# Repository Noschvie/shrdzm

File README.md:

## SHRDZM is intended to become an end-to-end integration platform.
It provides wiring digrams, source code and working examples.
Also plug-ins for most commonly used home automation solutions will be collected.

To build cheap integrations of many kind of sensors and/or actors into your own automation solution with the focus on energy efficiancy (battery operated devices) and simpleness.

Take a look on the [Wiki](https://github.com/saghonfly/shrdzm/wiki)

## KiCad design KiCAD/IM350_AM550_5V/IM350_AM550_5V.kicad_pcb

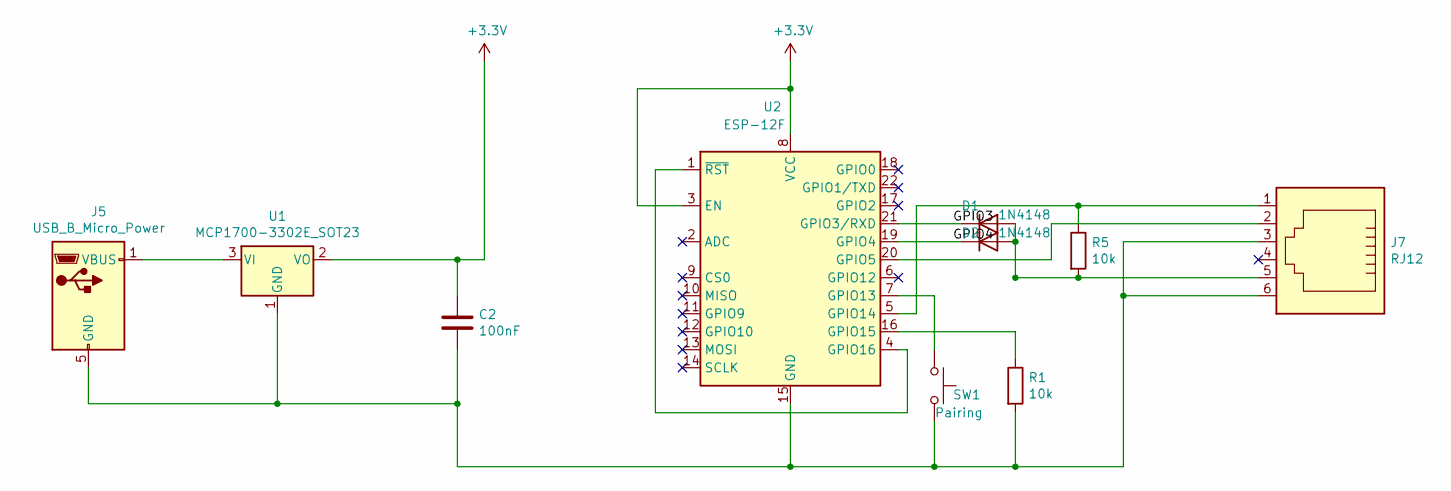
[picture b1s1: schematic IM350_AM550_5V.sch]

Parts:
C2: 100nF; C_Disc_D6.0mm_W2.5mm_P5.00mm
D1, D2: 1N4148; D_0805_2012Metric_Pad1.15x1.40mm_HandSolder
J5: USB_B_Micro_Power; USB_Micro-B_Power
J7: RJ12; RJ12_Amphenol_54601_Reduced
R1, R5: 10k; R_Axial_DIN0207_L6.3mm_D2.5mm_P2.54mm_Vertical
SW1: Pairing; SW_PUSH_6mm
U1: MCP1700-3302E_SOT23; SOT-23_Handsoldering
U2: ESP-12F; ESP-12E

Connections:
+3V3: C2.1, U1.2 (VO), U2.3 (EN), U2.8 (VCC)
/GPIO3: D1.1 (K), U2.21 (GPIO3/RXD)
/GPIO4: D2.1 (K), U2.19 (GPIO4)
unnamed: C2.2, J5.5 (GND), J7.3, J7.6, R1.2, SW1.2, U1.1 (GND), U2.15 (GND)
unnamed: D1.2 (A), D2.2 (A), J7.5, R5.2
unnamed: J5.1 (VBUS), U1.3 (VI)
unnamed: J7.1, R5.1, U2.5 (GPIO14)
unnamed: J7.2, U2.20 (GPIO5)
unnamed: R1.1, U2.16 (GPIO15)
unnamed: SW1.1, U2.7 (GPIO13)
unnamed: U2.1 (~RST), U2.4 (GPIO16)

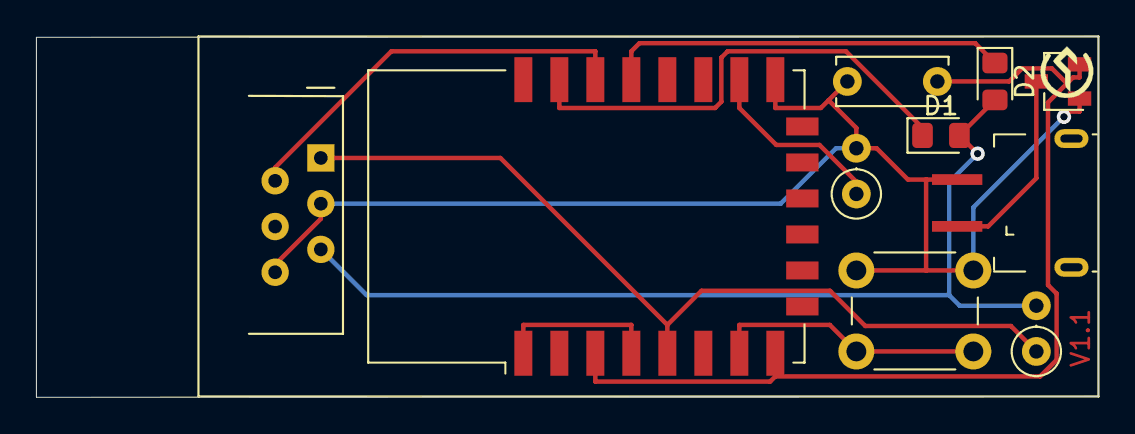
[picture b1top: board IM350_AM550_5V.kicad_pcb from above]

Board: 2 copper layers, 59.0 x 20.0 mm, 12 parts (1 on the bottom side), 11 nets.

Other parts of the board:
G1: LOGO; SHRDZM 22x7
G2: LOGO; SHRDZM Symbol 3x3

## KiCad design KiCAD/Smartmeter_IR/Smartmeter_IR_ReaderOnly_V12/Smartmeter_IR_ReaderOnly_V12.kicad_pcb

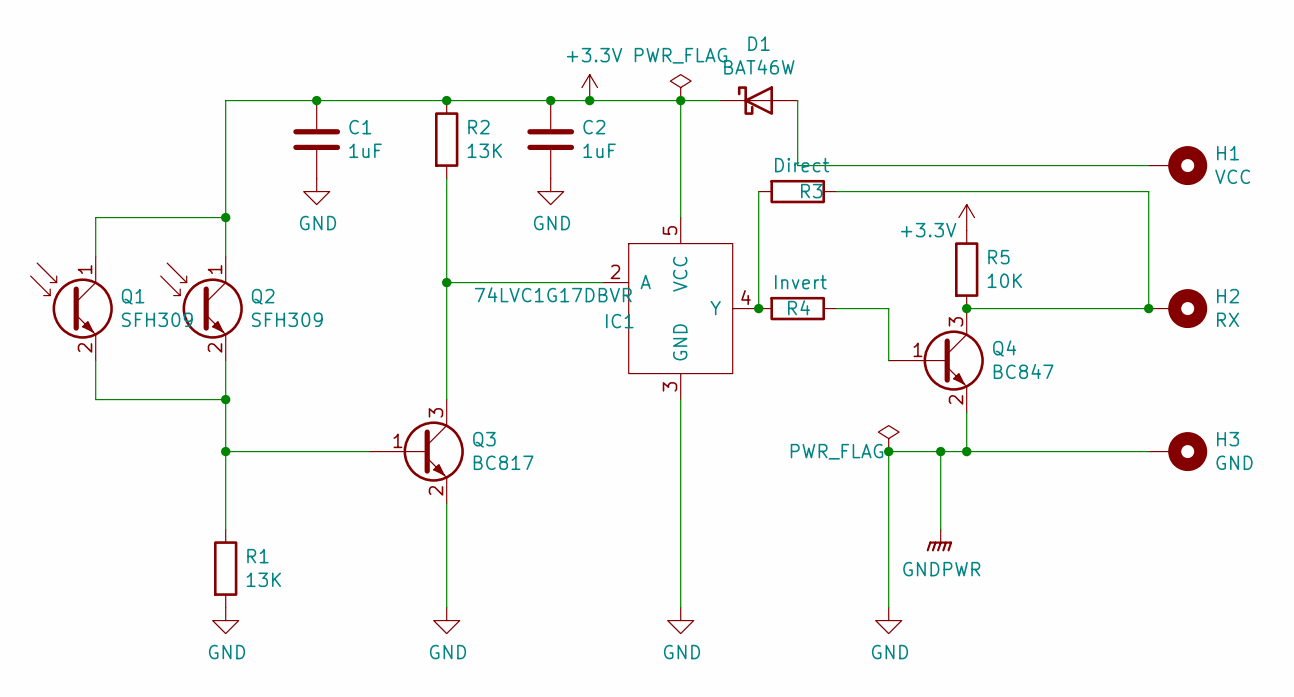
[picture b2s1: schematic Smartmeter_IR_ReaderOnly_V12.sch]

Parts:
C1, C2: 1uF; C_0603_1608Metric_Pad1.08x0.95mm_HandSolder
D1: BAT46W; D_SOD-123
H1: VCC; SolderWirePad_1x01_SMD_1x2mm
H2: RX; SolderWirePad_1x01_SMD_1x2mm
H3: GND; SolderWirePad_1x01_SMD_1x2mm
IC1: 74LVC1G17DBVR; SOT-23-5
Q1, Q2: SFH309; LED_D3.0mm
Q3: BC817; SOT-23
Q4: BC847; SOT-23
R1, R2: 13K; R_0603_1608Metric_Pad0.98x0.95mm_HandSolder
R3: Direct; R_0402_1005Metric_Pad0.72x0.64mm_HandSolder
R4: Invert; R_0402_1005Metric_Pad0.72x0.64mm_HandSolder
R5: 10K; R_0603_1608Metric_Pad0.98x0.95mm_HandSolder

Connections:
+3V3: C1.1, C2.1, D1.1 (K), IC1.5 (VCC), Q1.1 (C), Q2.1 (C), R2.1, R5.1
GND: C1.2, C2.2, H3.1, IC1.3 (GND), Q3.2 (E), Q4.2 (E), R1.2
unnamed: D1.2 (A), H1.1
unnamed: H2.1, Q4.3 (C), R3.1, R5.2
unnamed: IC1.2 (A), Q3.3 (C), R2.2
unnamed: IC1.4 (Y), R3.2, R4.2
unnamed: Q1.2 (E), Q2.2 (E), Q3.1 (B), R1.1
unnamed: Q4.1 (B), R4.1

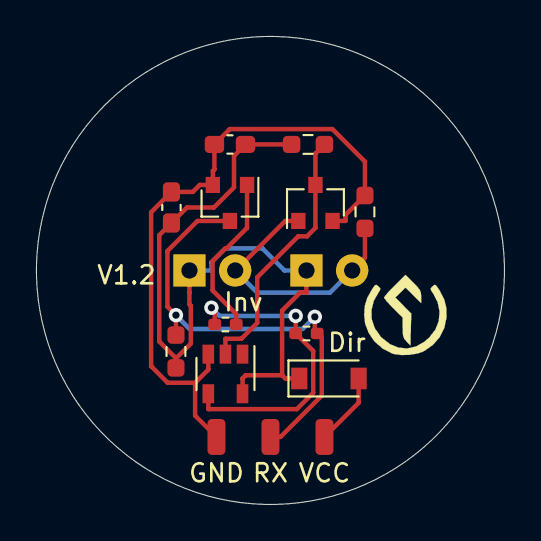
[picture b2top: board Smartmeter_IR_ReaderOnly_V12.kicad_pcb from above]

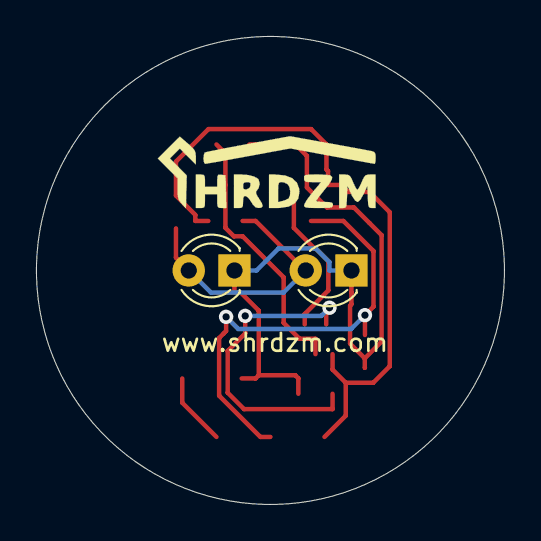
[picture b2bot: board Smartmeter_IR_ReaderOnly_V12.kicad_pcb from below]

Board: 2 copper layers, 26.0 x 26.0 mm, 18 parts (3 on the bottom side), 8 nets.

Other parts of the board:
G1: LOGO; SHRDZM 12x4
G2: LOGO; SHRDZM Symbol 5x5

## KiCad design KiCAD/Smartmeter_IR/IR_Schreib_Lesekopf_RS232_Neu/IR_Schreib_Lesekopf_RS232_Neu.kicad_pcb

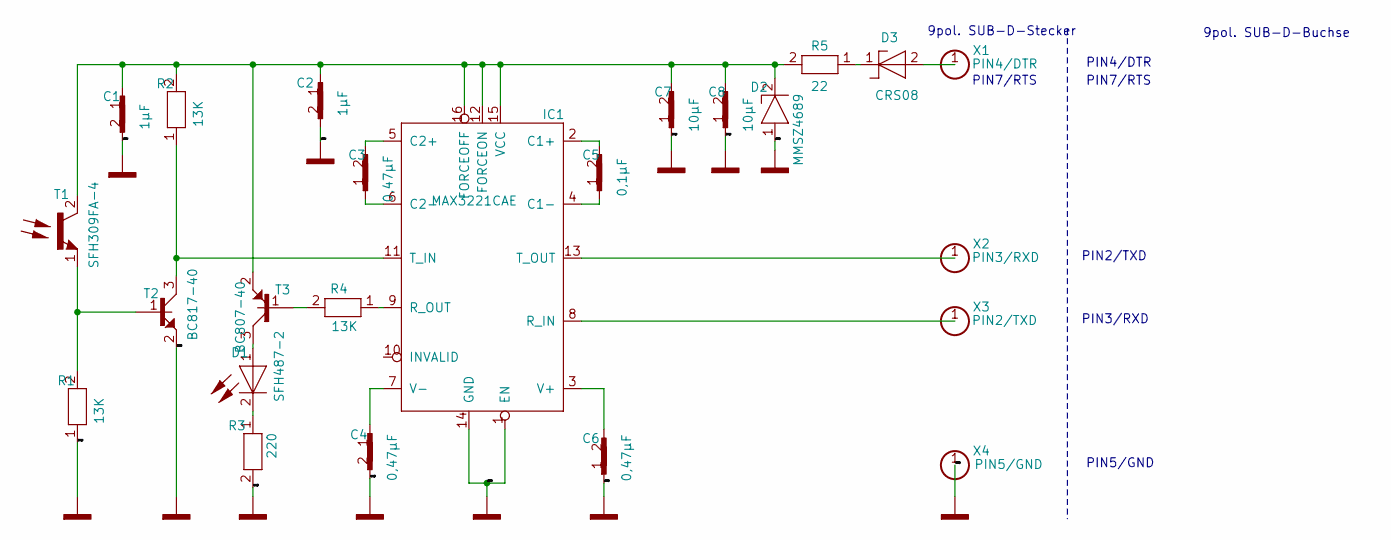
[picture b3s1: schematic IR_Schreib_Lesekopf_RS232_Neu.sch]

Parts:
C1: 1µF; 0603_KLEIN_25
C2: 1µF; 1206_29
C3: 0,47µF; 0603_13
C4: 0,47µF; 0603_0
C5: 0,1µF; 0603_12
C6: 0,47µF; 0603_1
C7: 10µF; 0805_KLEIN_34
C8: 10µF; 0805_KLEIN_2
D1: SFH487-2; LED_3MM_26
D2: MMSZ4689; DO214AA_15
D3: CRS08; SOD123_17
IC1: MAX3221CAE; SSOP16_11
R1: 13K; 0603_KLEIN_20
R2: 13K; 0603_KLEIN_21
R3: 220; 0603_KLEIN_31
R4: 13K; 0603_KLEIN_27
R5: 22; 1206_18
T1: SFH309FA-4; FOTO_4MM_19
T2: BC817-40; SOT23_3_33
T3: BC807-40; SOT23_3_32
X1: PIN4/DTR; LOETPUNKT_7
X2: PIN3/RXD; LOETPUNKT_9
X3: PIN2/TXD; LOETPUNKT_8
X4: PIN5/GND; LOETPUNKT_10

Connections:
1: C1.2, C2.2, C4.2, C6.1, C7.1, C8.1, D2.1, IC1.1 (EN), IC1.14 (GND), R1.1, R3.2, T2.2, X4.1
unnamed: C1.1, C2.1, C7.2, C8.2, D2.2, IC1.12 (FORCEON), IC1.15 (VCC), IC1.16 (FORCEOFF), R2.2, R5.2, T1.2, T3.2
unnamed: C3.1, IC1.6 (C2-)
unnamed: C3.2, IC1.5 (C2+)
unnamed: C4.1, IC1.7 (V-)
unnamed: C5.1, IC1.4 (C1-)
unnamed: C5.2, IC1.2 (C1+)
unnamed: C6.2, IC1.3 (V+)
unnamed: D1.2, R3.1
unnamed: D3.1, R5.1
unnamed: D3.2, X1.1
unnamed: IC1.8 (R_IN), X3.1
unnamed: IC1.9 (R_OUT), R4.1
unnamed: IC1.11 (T_IN), R2.1
unnamed: IC1.13 (T_OUT), X2.1
unnamed: R1.2, T1.1

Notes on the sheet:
9pol. SUB-D-Stecker
PIN7/RTS
PIN4/DTR
PIN2/TXD
PIN3/RXD
PIN5/GND
9pol. SUB-D-Buchse

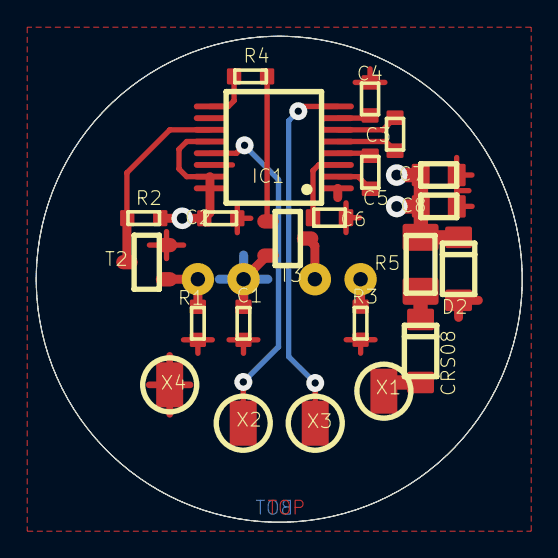
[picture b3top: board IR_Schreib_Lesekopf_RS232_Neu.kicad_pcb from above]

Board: 2 copper layers, 27.0 x 27.0 mm, 24 parts (0 on the bottom side), 16 nets.

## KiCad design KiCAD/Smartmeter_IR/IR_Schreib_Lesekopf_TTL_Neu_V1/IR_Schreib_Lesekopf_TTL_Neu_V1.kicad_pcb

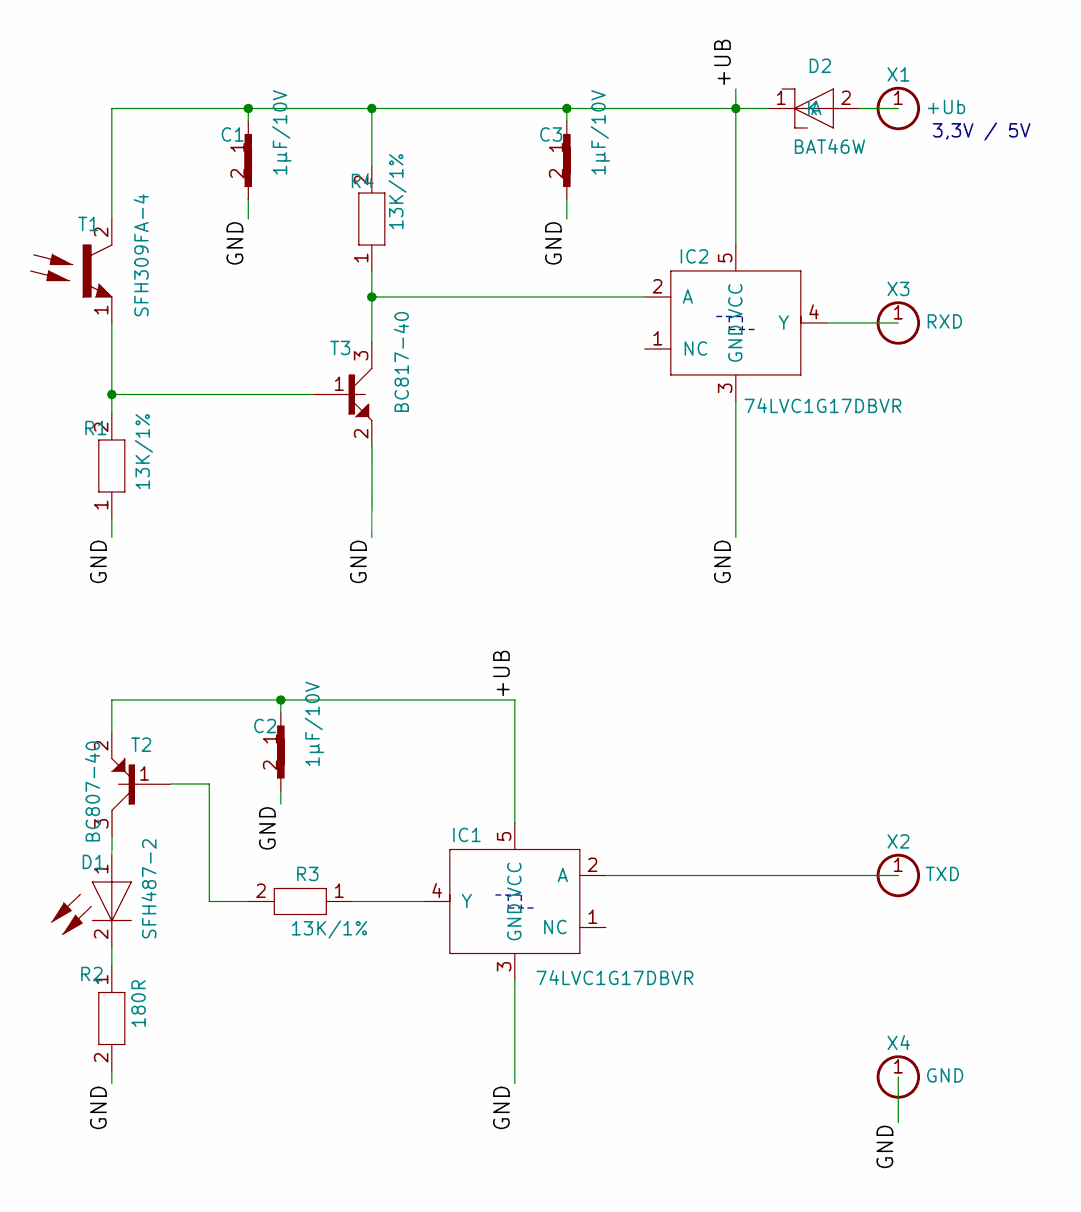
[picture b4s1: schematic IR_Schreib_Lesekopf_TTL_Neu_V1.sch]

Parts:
C1: 1µF/10V; 0805_11
C2: 1µF/10V; 0805_21
C3: 1µF/10V; 0805_10
D1: SFH487-2; LED_3MM_13
D2: BAT46W; SOD123_25
IC1: 74LVC1G17DBVR; SOT23_5_20
IC2: 74LVC1G17DBVR; SOT23_5_23
R1: 13K/1%; 0805_5
R2: 180R; 0805_27
R3: 13K/1%; 0805_14
R4: 13K/1%; 0805_6
T1: SFH309FA-4; FOTO_4MM_4
T2: BC807-40; SOT23_3_28
T3: BC817-40; SOT23_3_26
X1: +Ub; LOETPUNKT_3
X2: TXD; LOETPUNKT_19
X3: RXD; LOETPUNKT_2
X4: GND; LOETPUNKT_1

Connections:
/+UB: C1.1, C2.1, C3.1, D2.1 (K), IC1.5 (VCC), IC2.5 (VCC), R4.2, T1.2
/GND: C1.2, C2.2, C3.2, IC1.3 (GND), IC2.3 (GND), R1.1, R2.2, X4.1
unnamed: D1.1, T2.3
unnamed: D1.2, R2.1
unnamed: D2.2 (A), X1.1
unnamed: IC1.2 (A), X2.1
unnamed: IC1.4 (Y), R3.1
unnamed: IC2.2 (A), R4.1, T3.3
unnamed: IC2.4 (Y), X3.1
unnamed: R1.2, T1.1, T3.1

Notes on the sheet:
3,3V / 5V

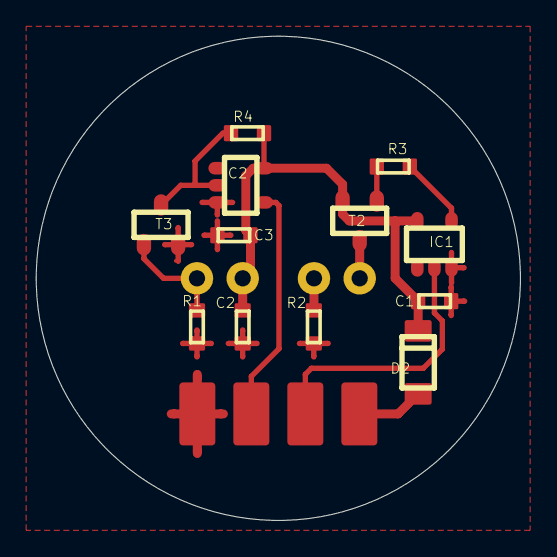
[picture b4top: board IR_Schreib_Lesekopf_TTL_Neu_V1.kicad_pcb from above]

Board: 2 copper layers, 26.9 x 26.9 mm, 18 parts (0 on the bottom side), 10 nets.

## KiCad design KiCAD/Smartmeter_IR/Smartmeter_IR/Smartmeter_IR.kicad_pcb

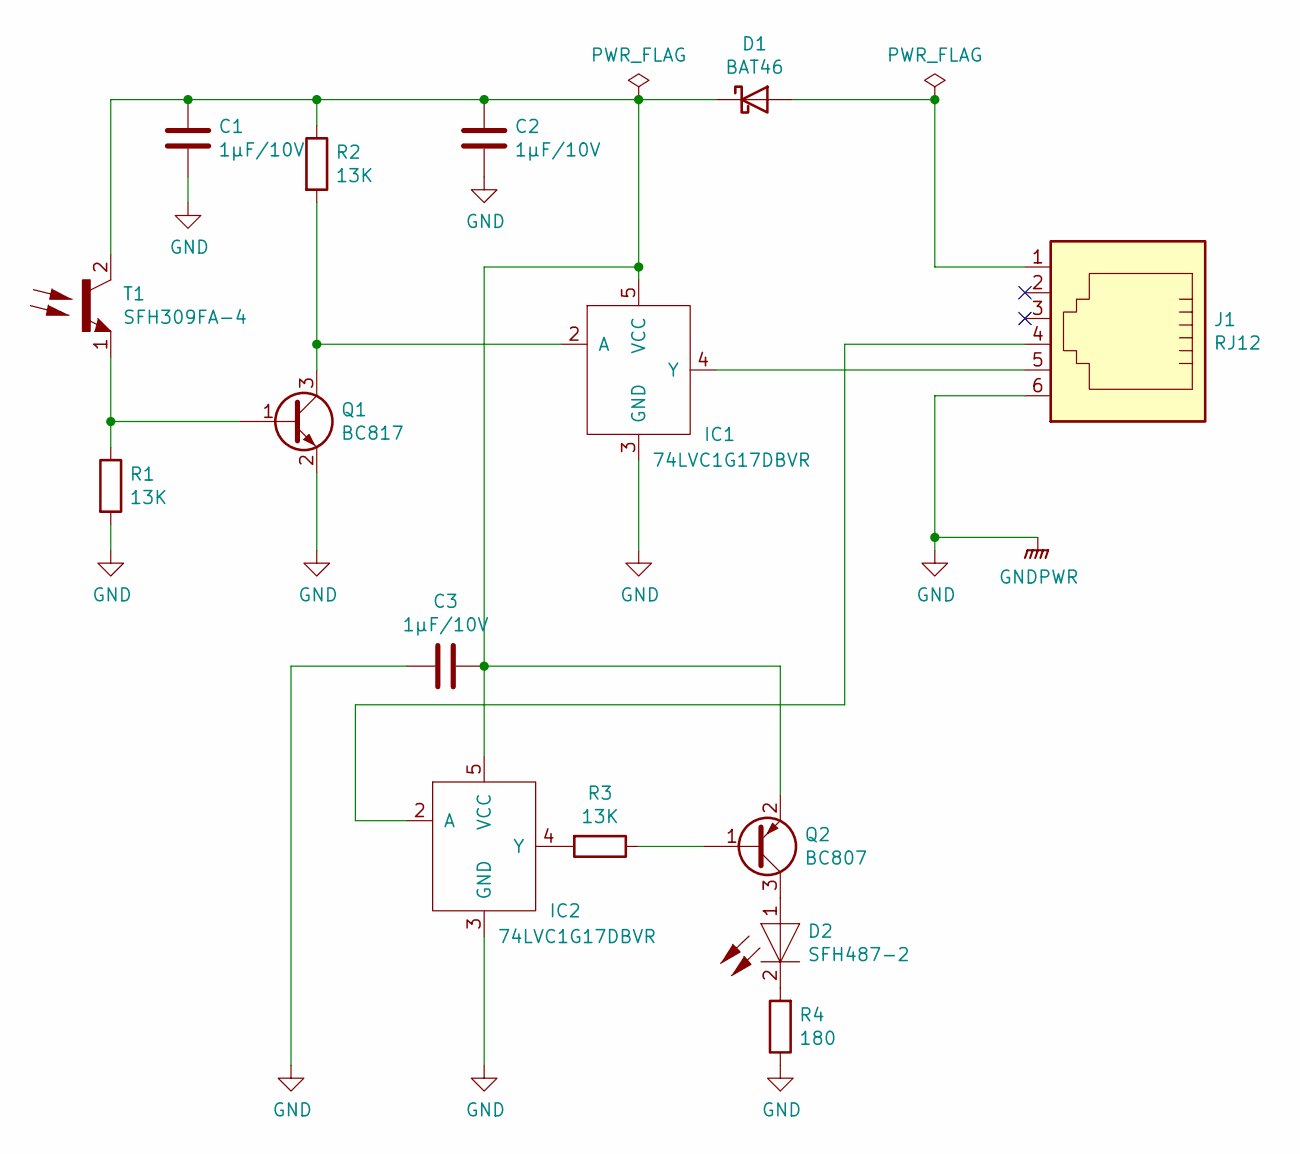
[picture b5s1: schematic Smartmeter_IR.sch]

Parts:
C1, C2, C3: 1µF/10V; C_0805_2012Metric_Pad1.18x1.45mm_HandSolder
D1: BAT46; D_SOD-123
D2: SFH487-2; LED_3MM_26
IC1, IC2: 74LVC1G17DBVR; SOT-23-5
J1: RJ12; RJ12_Amphenol_54601
Q1: BC817; SOT-23
Q2: BC807; SOT-23
R1, R2, R3: 13K; R_0805_2012Metric_Pad1.20x1.40mm_HandSolder
R4: 180; R_0805_2012Metric_Pad1.20x1.40mm_HandSolder
T1: SFH309FA-4; FOTO_4MM_19

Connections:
GND: C1.2, C2.2, C3.2, IC1.3 (GND), IC2.3 (GND), J1.6, Q1.2 (E), R1.2, R4.1
unnamed: C1.1, C2.1, C3.1, D1.1 (K), IC1.5 (VCC), IC2.5 (VCC), Q2.2 (E), R2.1, T1.2
unnamed: D1.2 (A), J1.1
unnamed: D2.1, Q2.3 (C)
unnamed: D2.2, R4.2
unnamed: IC1.2 (A), Q1.3 (C), R2.2
unnamed: IC1.4 (Y), J1.5
unnamed: IC2.2 (A), J1.4
unnamed: IC2.4 (Y), R3.2
unnamed: Q1.1 (B), R1.1, T1.1
unnamed: Q2.1 (B), R3.1

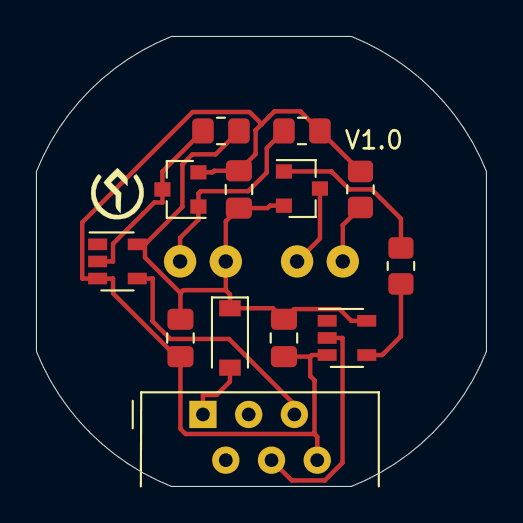
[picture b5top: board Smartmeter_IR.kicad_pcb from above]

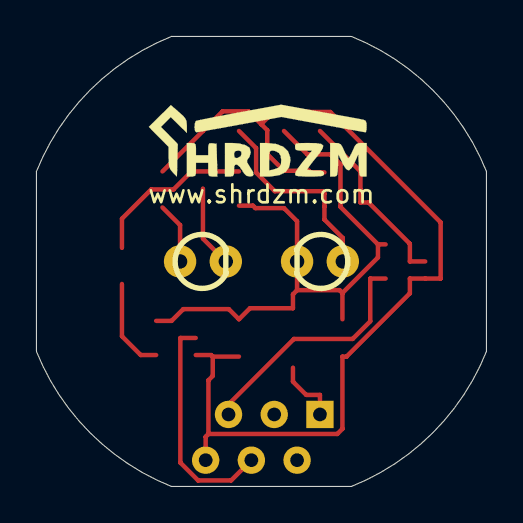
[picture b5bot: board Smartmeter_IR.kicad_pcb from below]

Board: 2 copper layers, 25.0 x 25.0 mm, 17 parts (2 on the bottom side), 11 nets.

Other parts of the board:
G1: LOGO; SHRDZM 12x4
G2: LOGO; SHRDZM Symbol 3x3

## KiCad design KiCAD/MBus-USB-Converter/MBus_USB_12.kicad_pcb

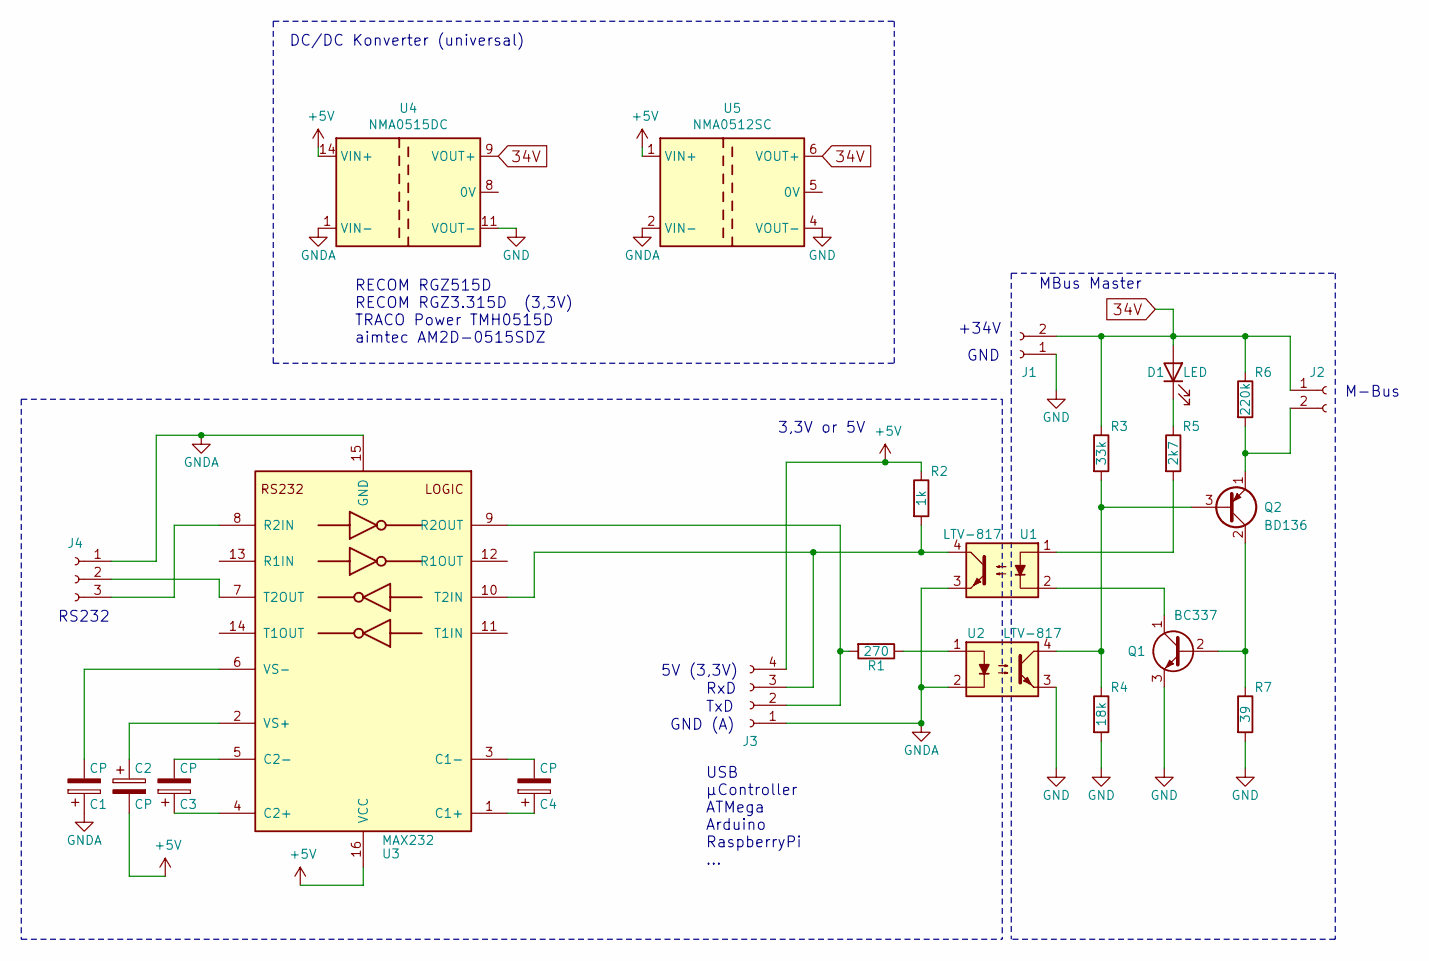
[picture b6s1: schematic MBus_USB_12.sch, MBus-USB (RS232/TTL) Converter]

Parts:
C1, C2, C3, C4: CP; CP_Radial_D5.0mm_P2.50mm
D1: LED; LED_D3.0mm
J1, J2: TerminalBlock_bornier-2_P5.08mm
J3: Conn_01x04_Female; TerminalBlock_bornier-4_P5.08mm
J4: Conn_01x03_Female; TerminalBlock_bornier-3_P5.08mm
Q1: BC337; TO-92_Molded_Wide_Oval
Q2: BD136; TO-126_Vertical
R1: 270; R_Axial_DIN0207_L6.3mm_D2.5mm_P10.16mm_Horizontal
R2: 1k; R_Axial_DIN0207_L6.3mm_D2.5mm_P10.16mm_Horizontal
R3: 33k; R_Axial_DIN0207_L6.3mm_D2.5mm_P10.16mm_Horizontal
R4: 18k; R_Axial_DIN0207_L6.3mm_D2.5mm_P10.16mm_Horizontal
R5: 2k7; R_Axial_DIN0207_L6.3mm_D2.5mm_P10.16mm_Horizontal
R6: 220k; R_Axial_DIN0207_L6.3mm_D2.5mm_P10.16mm_Horizontal
R7: 39; R_Axial_DIN0207_L6.3mm_D2.5mm_P10.16mm_Horizontal
U1, U2: LTV-817; DIP-4_W7.62mm_LongPads
U3: MAX232; DIP-16_W7.62mm_LongPads
U4: NMA0515DC; DCDC-Conv_muRata_NMAxxxxDC
U5: NMA0512SC; DCDC-Conv_muRata_NMAxxxxSC

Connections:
34V: D1.2 (A), J1.2, J2.1, R3.1, R6.1, U4.9 (VOUT+), U5.6 (VOUT+)
+5V: C2.2, J3.4, R2.1, U3.16 (VCC), U4.14 (VIN+), U5.1 (VIN+)
GND: J1.1, Q1.3 (E), R4.2, R7.2, U2.3, U4.11 (VOUT-), U5.4 (VOUT-)
GNDA: C1.1, J3.1, J4.1, U1.3, U2.2, U3.15 (GND), U4.1 (VIN-), U5.2 (VIN-)
unnamed: C1.2, U3.6 (VS-)
unnamed: C2.1, U3.2 (VS+)
unnamed: C3.1, U3.4 (C2+)
unnamed: C3.2, U3.5 (C2-)
unnamed: C4.1, U3.1 (C1+)
unnamed: C4.2, U3.3 (C1-)
unnamed: D1.1 (K), R5.1
unnamed: J2.2, Q2.1 (E), R6.2
unnamed: J3.2, R1.2, U3.9 (R2OUT)
unnamed: J3.3, R2.2, U1.4, U3.10 (T2IN)
unnamed: J4.2, U3.7 (T2OUT)
unnamed: J4.3, U3.8 (R2IN)
unnamed: Q1.1 (C), U1.2
unnamed: Q1.2 (B), Q2.2 (C), R7.1
unnamed: Q2.3 (B), R3.2, R4.1, U2.4
unnamed: R1.1, U2.1
unnamed: R5.2, U1.1

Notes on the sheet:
3,3V or 5V
RxD
TxD
USB µController ATMega Arduino RaspberryPi ...
MBus Master
+34V
GND
GND (A)
5V (3,3V)
DC/DC Konverter (universal)
RECOM RGZ515D RECOM RGZ3.315D (3,3V) TRACO Power TMH0515D aimtec AM2D-0515SDZ
RS232
M-Bus

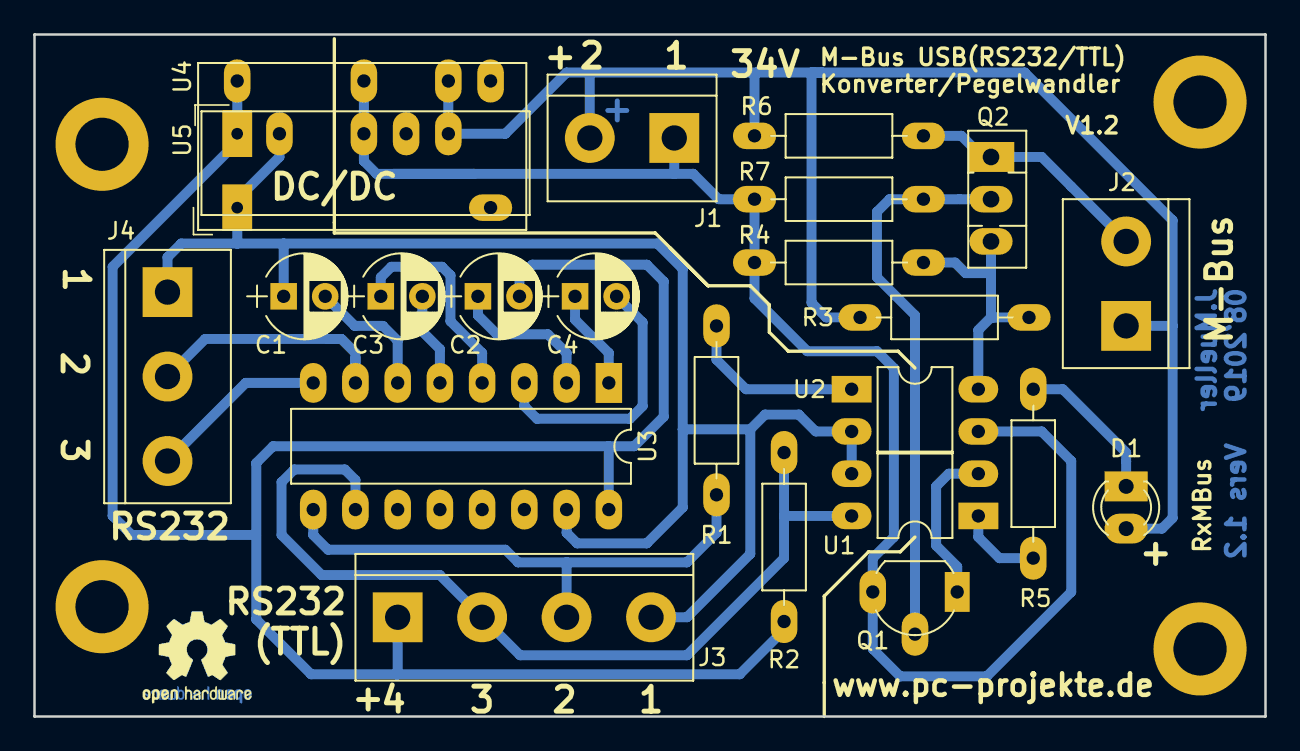
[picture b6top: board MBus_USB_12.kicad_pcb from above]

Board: 2 copper layers, 74.0 x 41.0 mm, 23 parts (0 on the bottom side), 21 nets.

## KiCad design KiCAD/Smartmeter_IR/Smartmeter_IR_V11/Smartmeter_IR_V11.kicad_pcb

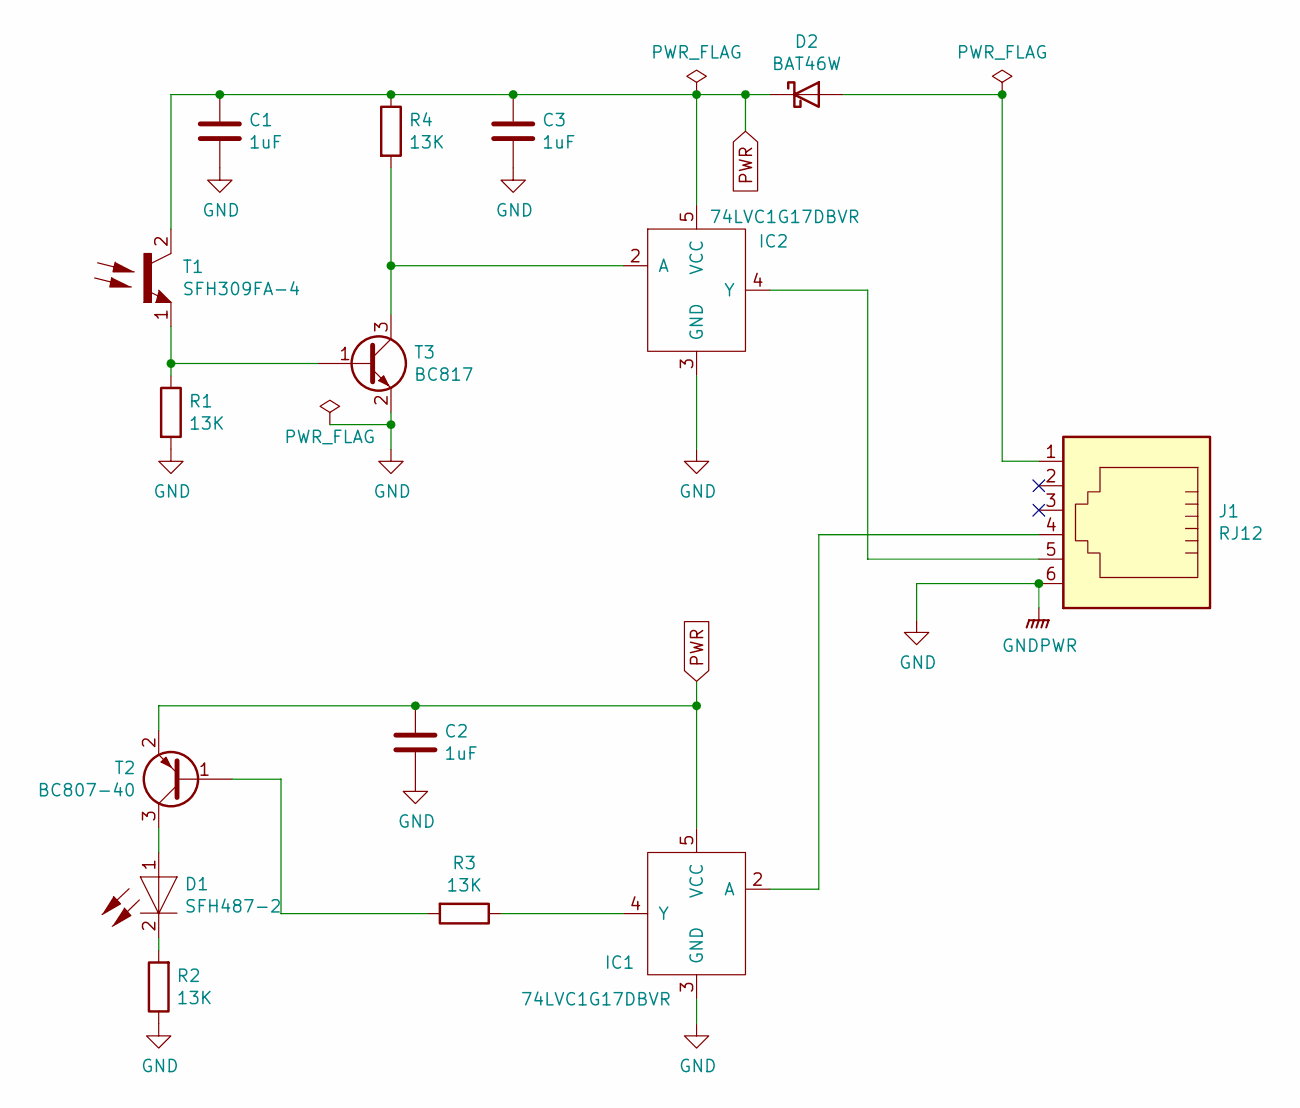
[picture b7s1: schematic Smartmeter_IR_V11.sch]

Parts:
C1, C2, C3: 1uF; C_0603_1608Metric_Pad1.08x0.95mm_HandSolder
D1: SFH487-2; LED_D3.0mm
D2: BAT46W; D_SOD-123
IC1, IC2: 74LVC1G17DBVR; SOT-23-5
J1: RJ12; RJ12_Amphenol_54601_Reduced
R1, R2, R3, R4: 13K; R_0603_1608Metric_Pad0.98x0.95mm_HandSolder
T1: SFH309FA-4; LED_D3.0mm
T2: BC807-40; SOT-23
T3: BC817; SOT-23

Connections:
GND: C1.2, C2.2, C3.2, IC1.3 (GND), IC2.3 (GND), J1.6, R1.2, R2.1, T3.2 (E)
unnamed: D1.1, T2.3 (C)
unnamed: D1.2, R2.2
unnamed: D2.2 (A), J1.1
unnamed: IC1.2 (A), J1.4
unnamed: IC1.4 (Y), R3.1
unnamed: IC2.2 (A), R4.2, T3.3 (C)
unnamed: IC2.4 (Y), J1.5
unnamed: R1.1, T1.1, T3.1 (B)
unnamed: R3.2, T2.1 (B)
PWR: C1.1, C2.1, C3.1, D2.1 (K), IC1.5 (VCC), IC2.5 (VCC), R4.1, T1.2, T2.2 (E)

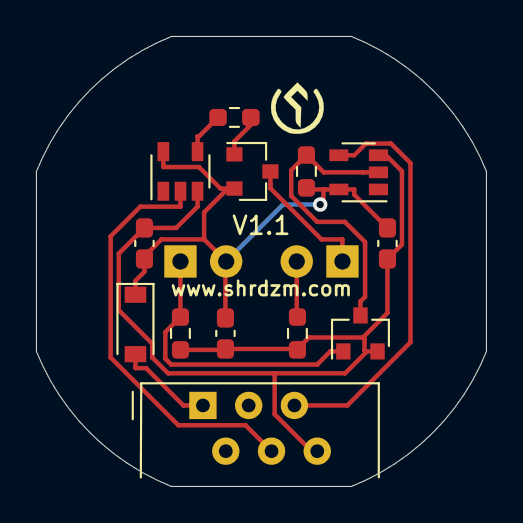
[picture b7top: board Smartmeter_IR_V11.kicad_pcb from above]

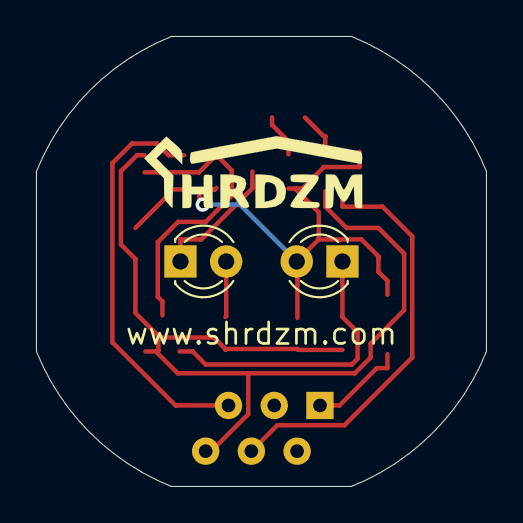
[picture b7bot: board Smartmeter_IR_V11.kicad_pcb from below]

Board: 2 copper layers, 25.0 x 25.0 mm, 15 parts (2 on the bottom side), 11 nets.

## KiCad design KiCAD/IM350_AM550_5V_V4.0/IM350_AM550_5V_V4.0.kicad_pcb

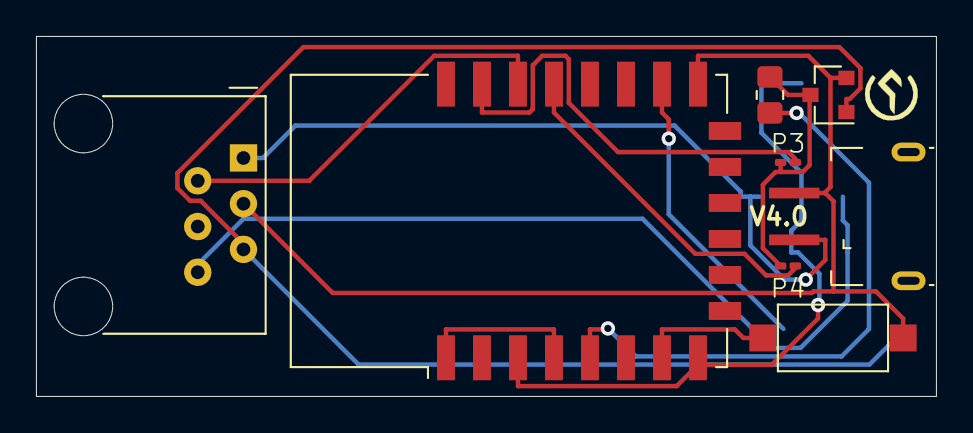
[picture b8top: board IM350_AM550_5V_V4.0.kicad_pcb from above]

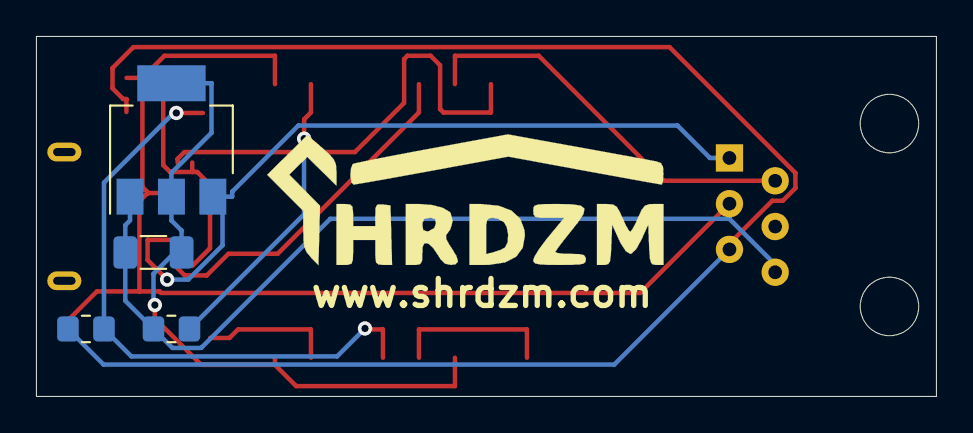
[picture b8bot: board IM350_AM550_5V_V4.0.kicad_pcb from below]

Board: 2 copper layers, 50.0 x 20.0 mm, 14 parts (5 on the bottom side), 12 nets.

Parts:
C1: 22uF; C_1206_3216Metric_Pad1.33x1.80mm_HandSolder
G1: LOGO; SHRDZM 22x7
G2: LOGO; SHRDZM Symbol 3x3
J1: USB_B_Micro_Power; USB_Micro-B_Power
J2: RJ12; RJ12_Amphenol_54601
P3, P4: 0; R_0201_0603Metric_Pad0.64x0.40mm_HandSolder
Q1: BC847; SOT-23
R3: 2.2k; R_0805_2012Metric_Pad1.20x1.40mm_HandSolder
R4, R5: 10k; R_0805_2012Metric_Pad1.20x1.40mm_HandSolder
SW1: SW_Push; SW_SPST_CK_RS282G05A3
U1: AMS1117-3.3; SOT-223-3_TabPin2
U2: ESP-12F; ESP-12E

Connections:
unnamed: C1.1, U1.2, U2.3, U2.8
unnamed: C1.2, J1.5, J2.3, J2.6, Q1.2, R3.2, SW1.2, U1.1, U2.15
unnamed: J1.1, J2.1, U1.3
unnamed: J2.2, U2.20
unnamed: J2.5, Q1.1, R5.2
unnamed: P3.1, P4.1, Q1.3, R4.2
unnamed: P3.2, U2.21
unnamed: P4.2, U2.19
unnamed: R3.1, U2.16
unnamed: R4.1, R5.1, U2.5
unnamed: SW1.1, U2.7
unnamed: U2.1, U2.4

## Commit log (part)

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2020-08-29 OTA for serial added
2020-10-20 IM350 added
2020-10-26 IM350 max read time changed
2020-11-06 IM350 updated
2020-12-07 Update Logo
2020-12-14 Update IM350 to inbuild decoding
2021-01-09 First version of 4th generation
2021-01-10 Back to 0.3.3
2021-01-16 Upgrade
2021-01-16 Upgrade to Version 0.4.0
2021-01-18 Auto Pairing added
2021-01-24 IM350 Picture Upload
2021-01-24 OTA for SHRDZMDevice added in Gateway Mode
2021-02-05 Dewpoint added for HTU21 sensor
2021-02-05 Heat Index added for DHT22 and HTU21
2021-02-06 SDS011_BH1750 added
2021-02-11 Water BOM added
2021-02-20 Update Wiring
2021-02-27 Doorsensor added
2021-03-04 IM350 Bugfix
2021-03-07 IM350 Correction
    IM350 was always showing same values in permanent online mode (Integration Style ZERO) due to uninitialited cipher object.
2021-03-20 KiCAD files added
2021-03-21 Doorsensor PCB added
2021-03-21 DOORSENSOR Updated
2021-03-23 SDS011 Circuit added
2021-03-25 DOORSENSOR state error added
2021-03-25 DOORSENSOR upgraded
2021-04-03 AM550 Smartmeter added
2021-04-04 IM350 SoftwareSerial added
2021-04-04 IM350 Invert Serial added
2021-04-07 IM350_AM550_5V Gerber files added
2021-04-10 Update 3D Models
2021-04-12 Bootreason added
2021-04-15 DOORSENSOR 9V KiCAD added
2021-05-05 Website last measurement values added
2021-05-23 IM350 Wels added
2021-05-24 IM350 Wels bug fix
2021-05-30 Experimental Cloud added
2021-05-31 Cloud REST added
2021-05-31 Cloud files added
2021-06-01 Cloud functions
2021-06-03 Refresh Cloud Token added
2021-06-03 Update Alexa Authentification
2021-06-03 Update Alexa
2021-06-04 Update Alexa Token Handling
2021-06-04 Logo update
2021-06-05 Update Alexa APi
2021-06-07 MQTTGateway SoftwareSerial fixed
2021-06-08 OTA Upgrade via Web Explorer
2021-07-04 Publish Checksum Error
2021-07-05 Cloud Server Files Update
2021-07-18 Changed Smartmeter to Crypto lib usage
2021-08-01 SmartMeter update
2021-08-01 Website update
2021-08-03 IM350 hourWatt added
2021-08-05 SmartMeter Statistic added
2021-08-08 Website handleSettings bugfix
2021-08-12 IM350 Cloud Update bugfix
2021-08-14 Smartmeter Description Updated
2021-08-15 SHRDZMGatewayMQTT Updated
2021-08-17 Update SHRDZMGatewayMQTT
2021-08-20 IM350 removed invalid values
2021-08-21 MQTT Connection set to optional
2021-10-06 Smartmeter Energie Steiermark added
2021-10-09 JSon send format added
2021-10-17 Smartmeter updated
2021-10-22 Private Cloud data send added to SHRDZMDevice
2021-10-25 Smartmeter IR Head added
2021-11-20 AM550 Smartmeter from Slovenia added
2021-11-21 Smartmeter AM550 end byte detection added
2021-11-23 Update AM550 Slovenia
2021-11-23 Base for Version 0.5.2
2022-01-01 MBus for Smartmeter added
2022-01-02 KiCAD update
2022-01-05 Smartmeter Vienna E450 added
2022-01-10 Smartmeter TINETZ added
2022-01-10 Update SHRDZM_www logo
2022-01-17 Added Smartmeter IR Vienna
2022-01-19 Styria Smartmeter enhanced
2022-01-30 Slovenia unencrypted AM550 Smartmeter added
2022-02-03 MQTT Topic corrected

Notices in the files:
KiCAD/MBus-USB-Converter/MBus_USB_12.sch:
OpenHardware Cern ohl version 1.2
